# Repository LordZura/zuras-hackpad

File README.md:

# Zura’s HackPad  
A fully custom Linux-focused macropad featuring 4 programmable hotkeys, a rotary encoder with push switch, RGB underglow, and a 0.91” I²C OLED display all powered by a Seeed XIAO RP2040.  
Designed, modeled, and routed entirely for the Hack Club *Blueprint* program.

---

## Features

### Current Working Features
These are implemented in `main.py` now.

#### 4 Macro Keys
- **CP** | Copy | Sends `Ctrl + C` |
- **FC** | Folder Create | Sends `Ctrl + Shift + N` |
- **OT** | Open Terminal | Sends `Ctrl + Alt + T` |
- **LFN** | Fn Lock | Sends `F14`|

#### Rotary Encoder
- Rotate: Volume Up / Down  
- Press: currently basic input (extended features planned)

#### RGB Underglow (SK6812 MINI)
- 2 LED chain  
- Controlled via GPIO0  
- Basic color output active (animations planned)

---

### Planned / Future Features

#### Smart Copy/Paste
- First press copies  
- Second press pastes  
- Clipboard-empty - paste anyway  

#### Encoder Modes
- Cycle between: Volume - Brightness - Media - Custom  

#### OLED Display
- Clipboard indicator  
- Volume & brightness  
- Battery/time  
- Overheat warning  
- Mode icons & animations  

---

## Bill of Materials (BOM)

Bill of Materials (BOM)

1. Seeed XIAO RP2040 – 1 piece  
   The main controller board.

2. MX-style switches – 4 pieces  
   Any standard Cherry MX compatible switches.

3. EC11 rotary encoder (with built-in button) – 1 piece  
   Has A/B pins and a push switch.

4. SK6812 Mini LEDs – 2 pieces  
   Addressable RGB LEDs, chained together.

5. 0.91" I2C OLED screen – 1 piece  
   Uses GND, VCC, SCL, and SDA.

6. 4-pin female header – 1 piece  
   For plugging in the OLED.

7. MX keycaps – 4 pieces  
   Any MX-compatible keycaps.

8. M3 screws + heat-set inserts – 4 sets  
   Used to assemble the case.

9. Custom PCB (2-layer) – 1 piece  
   Smaller than 100×100 mm.

---

## System Layout  
(Directly from KiCad nets)

### Switches - XIAO
- SW1 - GPIO26  
- SW2 - GPIO27  
- SW3 - GPIO28  
- SW4 - GPIO29  

### Rotary Encoder
- A - GPIO2  
- B - GPIO4  
- C - GND  

### RGB LEDs (SK6812)
- MCU GPIO0 - D1 DIN  
- D1 DOUT - D2 DIN  
- VDD - +5V  
- VSS - GND  

### OLED Header (J1)
- Pin 1 - GND  
- Pin 2 - 3V3  
- Pin 3 - SCL (GPIO7)  
- Pin 4 - SDA (GPIO6)

---

## Project Structure

```
zuras-hackpad/
├── CAD/
│   ├── HackPad_Bottom.step
│   ├── HackPad_Top.step
│   └── HackPad_Assembly.step
├── PCB/
│   ├── HackPad.kicad_pro
│   ├── HackPad.kicad_sch
│   └── HackPad.kicad_pcb
├── Firmware/
│   └── main.py
├── Images/
│   ├── Bottom.png
│   ├── Debug.png
│   ├── Full.png
│   ├── PDC-Back.png
│   ├── PDC-Finish.png
│   ├── PDC-Front.png
│   ├── Schematic.png
│   └── Top.png
└── README.md
```

---

## Required Screenshots

### Top View  

### Bottom View  

### Assembled Case With All The Components

### PCB – Front  

### PCB – Back  

### PCB – Final Routing  

### Schematic  

### Debug  

---

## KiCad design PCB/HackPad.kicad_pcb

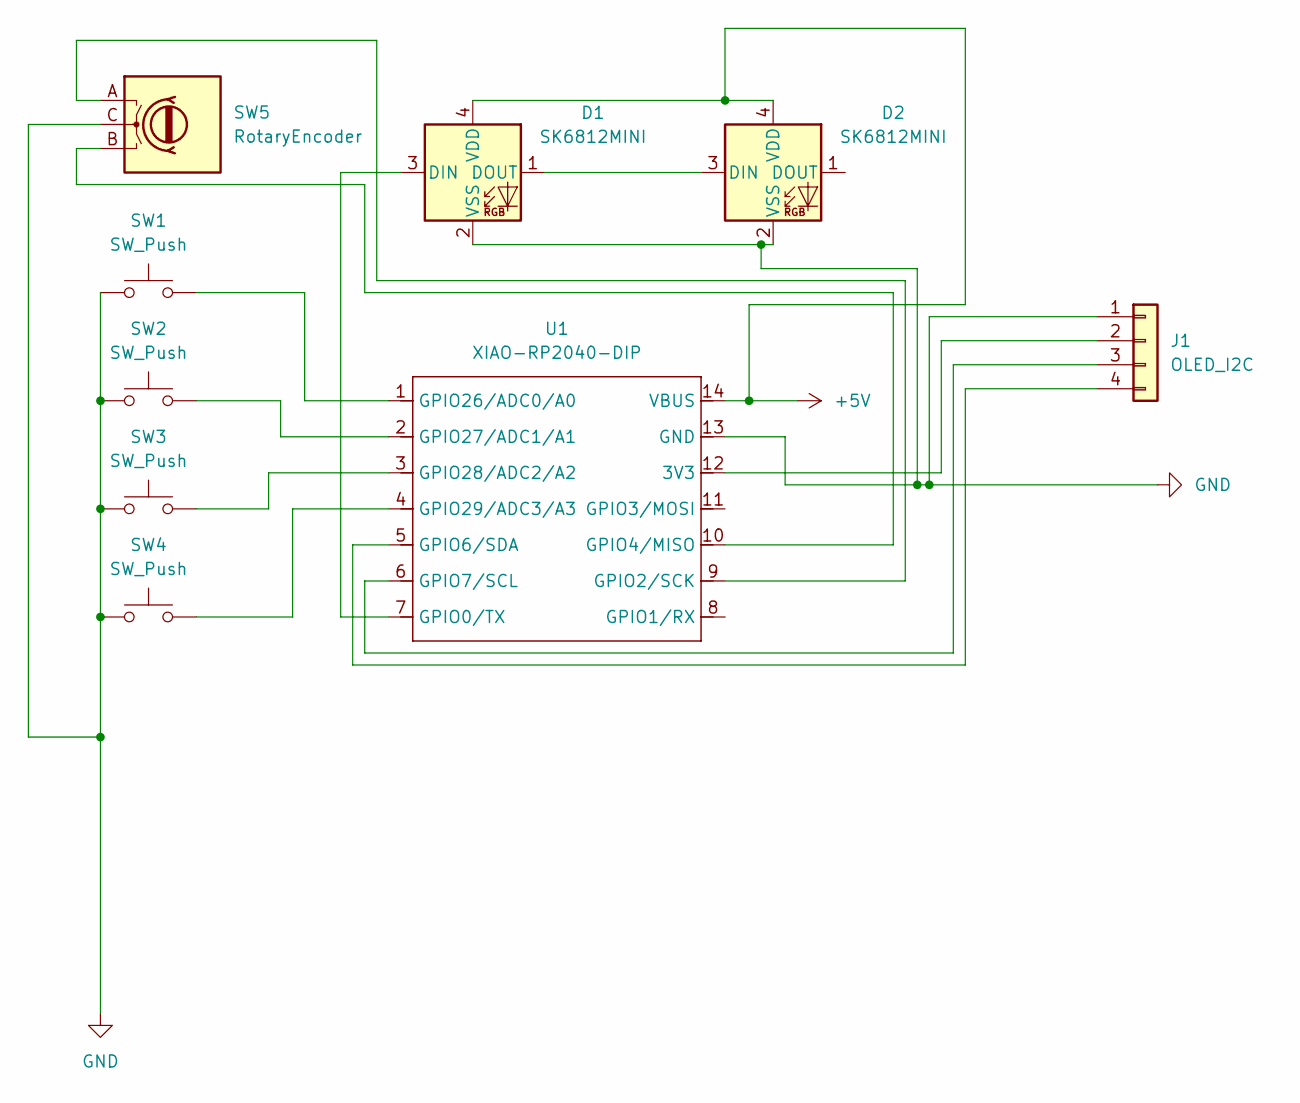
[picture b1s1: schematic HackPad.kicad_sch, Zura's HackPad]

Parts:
D1, D2: SK6812MINI; LED_SK6812MINI_PLCC4_3.5x3.5mm_P1.75mm
J1: OLED_I2C; PinSocket_1x04_P2.54mm_Vertical
SW1, SW2, SW3, SW4: SW_Push; SW_Cherry_MX_1.00u_PCB
SW5: RotaryEncoder; RotaryEncoder_Alps_EC11E-Switch_Vertical_H20mm
U1: XIAO-RP2040-DIP

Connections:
+5V: D1.4 (VDD), D2.4 (VDD), U1.14 (VBUS)
GND: D1.2 (VSS), D2.2 (VSS), J1.1, SW1.1, SW2.1, SW3.1, SW4.1, SW5.C, U1.13 (GND)
unnamed: D1.3 (DIN), U1.7 (GPIO0/TX)
unnamed: D1.1 (DOUT), D2.3 (DIN)
unnamed: J1.2, U1.12 (3V3)
unnamed: J1.3, U1.6 (GPIO7/SCL)
unnamed: J1.4, U1.5 (GPIO6/SDA)
unnamed: SW5.A, U1.9 (GPIO2/SCK)
unnamed: SW5.B, U1.10 (GPIO4/MISO)
unnamed: SW1.2, U1.1 (GPIO26/ADC0/A0)
unnamed: SW2.2, U1.2 (GPIO27/ADC1/A1)
unnamed: SW3.2, U1.3 (GPIO28/ADC2/A2)
unnamed: SW4.2, U1.4 (GPIO29/ADC3/A3)

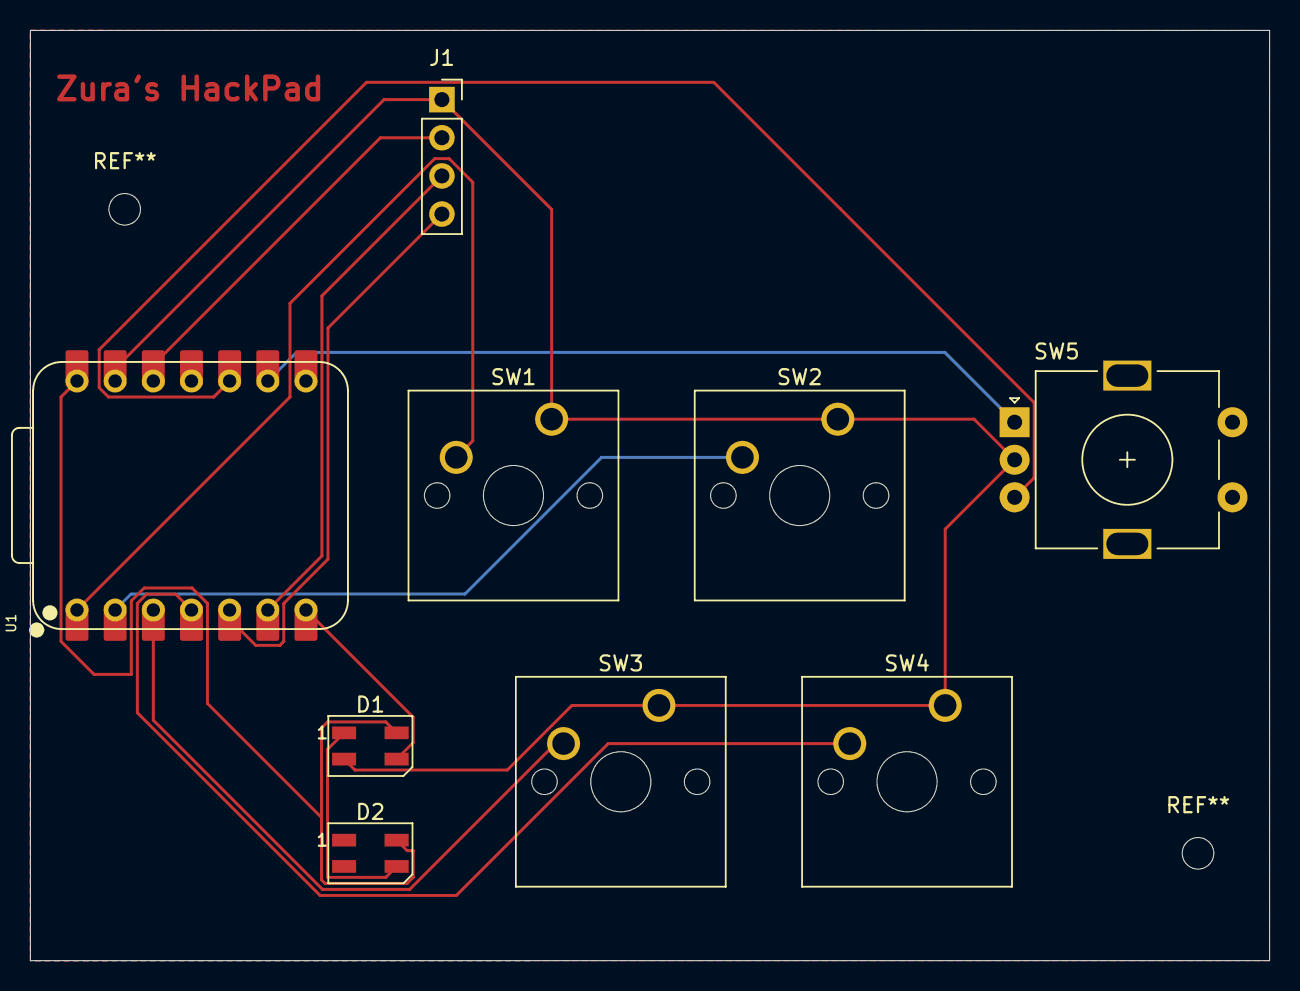
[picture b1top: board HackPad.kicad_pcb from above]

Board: 2 copper layers, 82.5 x 61.9 mm, 9 parts (0 on the bottom side), 13 nets.

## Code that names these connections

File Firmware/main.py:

# main.py for Zura's HackPad
#
# Hardware (from KiCad netlist):
# - SW1 → GPIO26/ADC0/A0
# - SW2 → GPIO27/ADC1/A1
# - SW3 → GPIO28/ADC2/A2
# - SW4 → GPIO29/ADC3/A3
# - Encoder A → GPIO2/SCK
# - Encoder B → GPIO4/MISO
# - SK6812 DIN → GPIO0/TX
# - OLED SDA → GPIO6/SDA
# - OLED SCL → GPIO7/SCL

import board

from kmk.kmk_keyboard import KMKKeyboard          # Core KMK keyboard class
from kmk.scanners.keypad import KeysScanner      # Simple per-pin key scanner
from kmk.keys import KC                          # Keycodes (Ctrl, etc.)
from kmk.modules.encoder import EncoderHandler   # Rotary encoder support
from kmk.extensions.media_keys import MediaKeys  # Volume/media keys


# -----------------------------
# PIN ASSIGNMENTS (from netlist)
# -----------------------------

# Switches: SW1..SW4 -> A0..A3
PIN_KEY_CP  = board.A0  # SW1 -> GPIO26/ADC0/A0
PIN_KEY_FC  = board.A1  # SW2 -> GPIO27/ADC1/A1
PIN_KEY_OT  = board.A2  # SW3 -> GPIO28/ADC2/A2
PIN_KEY_LFN = board.A3  # SW4 -> GPIO29/ADC3/A3

# Rotary encoder A/B (no push switch wired)
PIN_ENC_A   = board.D8  # GPIO2/SCK
PIN_ENC_B   = board.D9  # GPIO4/MISO

# RGB LED data in (first SK6812 DIN)
PIN_RGB_DIN = board.D6  # GPIO0/TX

# OLED I2C (header J1)
PIN_OLED_SDA = board.SDA  # GPIO6/SDA
PIN_OLED_SCL = board.SCL  # GPIO7/SCL


# -----------------------------
# KMK keyboard setup
# -----------------------------

keyboard = KMKKeyboard()  # Create keyboard instance

# 1×4 matrix for the 4 switches (CP, FC, OT, LFN)
key_pins = (
    PIN_KEY_CP,
    PIN_KEY_FC,
    PIN_KEY_OT,
    PIN_KEY_LFN,
)

keyboard.matrix = KeysScanner(
    pins=key_pins,             # list of GPIOs for each key
    value_when_pressed=False,  # active-low (pins go to GND when pressed)
    pull=True,                 # enable internal pull-ups
)

# Add media keys + encoder support
keyboard.extensions.append(MediaKeys())     # enable KC.VOLU / KC.VOLD etc.
encoder_handler = EncoderHandler()
keyboard.modules.append(encoder_handler)


# -----------------------------
# Encoder configuration
# -----------------------------

# One encoder: (A, B, switch_pin_or_None)
encoder_handler.pins = (
    (PIN_ENC_A, PIN_ENC_B, None),  # Only rotation, no switch
)

# Encoder map:
# For each layer, for each encoder: (CCW, CW)
# Layer 0, encoder 0 -> Volume Down / Volume Up
encoder_handler.map = [
    (
        (KC.VOLD, KC.VOLU),  # layer 0
    ),
]


# -----------------------------
# Keymap
# -----------------------------
# Key order in matrix: [CP, FC, OT, LFN]

# Common shortcuts
CP_COPY    = KC.LCTL(KC.C)              # Ctrl+C
CP_PASTE   = KC.LCTL(KC.V)              # Ctrl+V
NEW_FOLDER = KC.LCTL(KC.LSFT(KC.N))     # Ctrl+Shift+N (new folder)
OPEN_TERM  = KC.LCTL(KC.LALT(KC.T))     # Ctrl+Alt+T (Linux terminal)
FN_LOCK    = KC.F14                     # Fake Fn-lock key (map F14 in OS to toggle Fn)

# For now: CP key just does copy. Later we can implement stateful copy/paste toggling.
keyboard.keymap = [
    [
        CP_COPY,       # SW1 -> CP
        NEW_FOLDER,    # SW2 -> FC
        OPEN_TERM,     # SW3 -> OT
        FN_LOCK,       # SW4 -> LFN
    ]
]


# -----------------------------
# Run the keyboard
# -----------------------------

if __name__ == "__main__":
    keyboard.go()

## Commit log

2025-12-05 initial project structure
2025-12-05 Revise README for Zura's HackPad details
    Updated README to provide detailed information about Zura's HackPad, including features, bill of materials, system layout, project structure, firmware responsibilities, build steps, submission checkl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
2025-12-05 Update README to simplify screenshot instructions
    Removed redundant screenshot requirements from README.
2025-12-05 Revise project images section in README
    Updated project images section with detailed views and added new images.
2025-12-05 brah
2025-12-05 Files
2025-12-05 photos
2025-12-05 Add initial keyboard firmware implementation
    Initial implementation of the keyboard firmware with pin assignments, encoder support, and keymap for shortcuts.
2025-12-05 Revise system layout and pin usage details
    Updated pin usage summary and formatting in README.
2025-12-05 Update build steps in README.md
    Added instructions for copying files to the USB drive.
2025-12-05 code structure
2025-12-05 Revise README for improved feature descriptions
    Updated README to enhance clarity and detail about features, components, and build steps.
2025-12-05 Refactor README formatting and content structure
2025-12-05 Update README header format
2025-12-05 Remove submission checklist and license sections
    Removed the submission checklist and license sections from the README.
2025-12-05 Update 3D model section with assembled case image
    Updated the 3D model section to include an image of the assembled case with all components.
2025-12-05 removed
2025-12-05 screnshott
2025-12-05 Update README with project structure details
    Added project structure section with directory layout.
2025-12-05 file updates
2025-12-05 removed files
2025-12-07 added gerber and drill zip
2025-12-07 Refactor README for clarity and formatting
    Updated formatting and improved clarity in the README.
2025-12-07 Fix duplicate macro key entries in README
    Removed duplicate macro key entries in README.
2025-12-08 stff
2025-12-08 changesss
